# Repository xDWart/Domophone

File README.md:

# Domophone
Релейный модуль расширения на NodeMCU для доработки домофона Wi-Fi'ем и протоколом MQTT

**Eagle** - рабочий проект EagleCAD (v.7.7.0)

**platformio.ini** - ini-файл проекта в среде PlatformIO (редактор Atom)

**src/** - исходные коды прошивки

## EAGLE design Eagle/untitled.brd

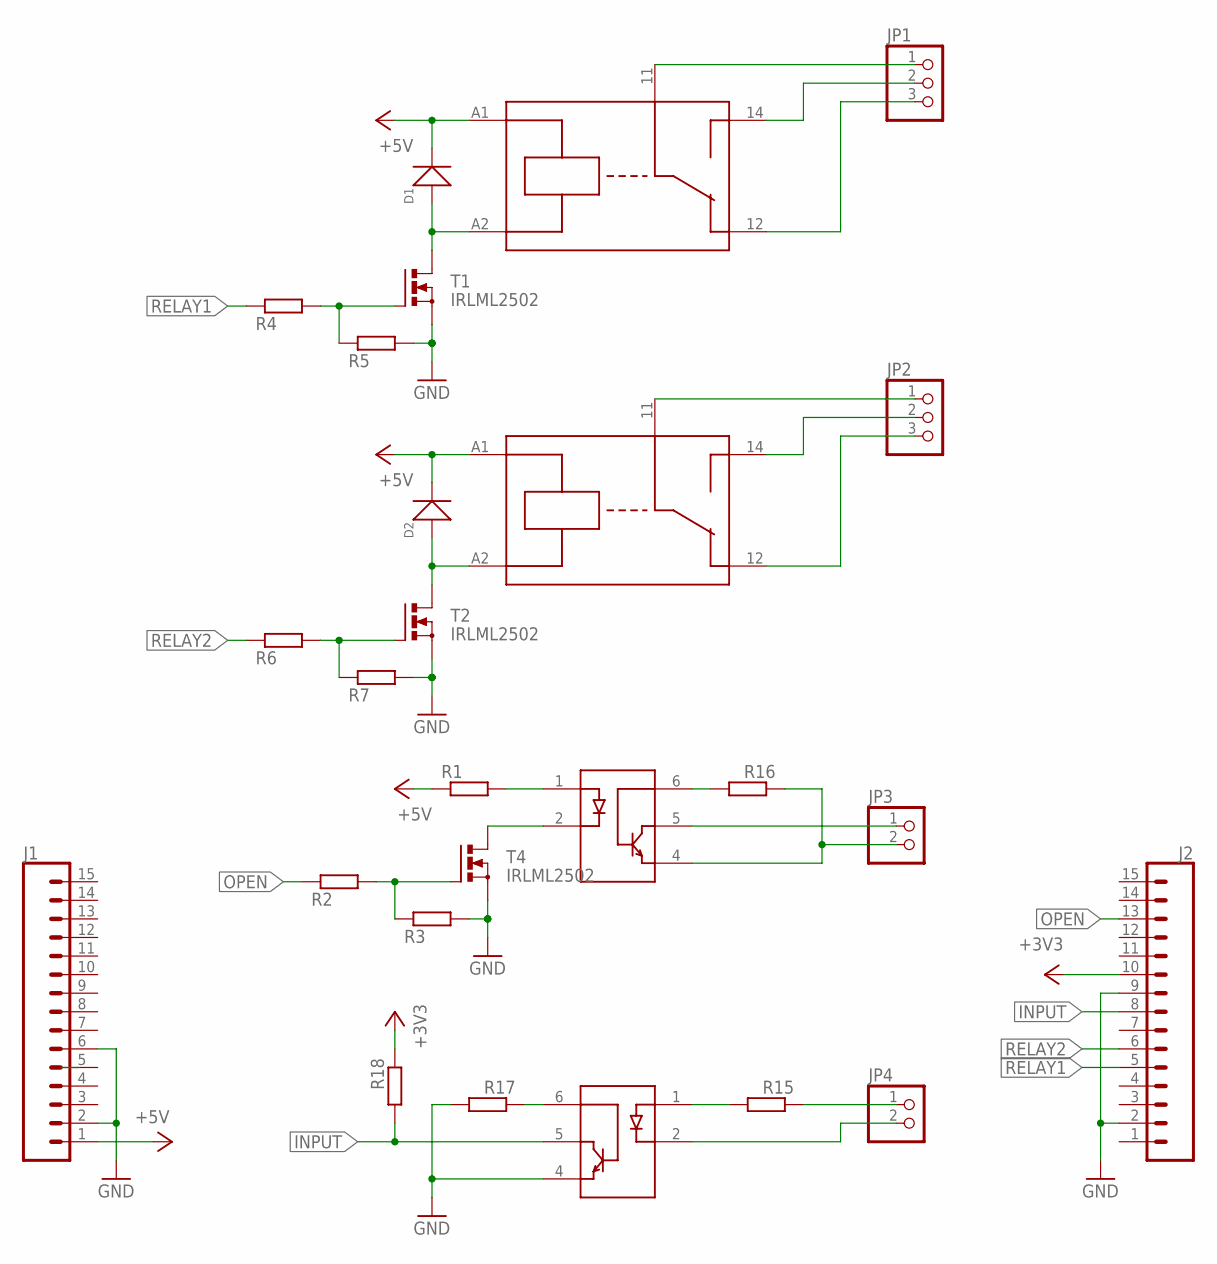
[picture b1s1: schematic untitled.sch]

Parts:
D1, D2: 1N4007; DO-214AC
J1, J2: CONN_15; 1X15
JP1, JP2: PINHD-1X3; 1X03
JP3, JP4: PINHD-1X2; 1X02
R1, R2, R3, R4, R5, R6, R7, R15, R16, R17, R18: R-EU_R0805; R0805
T1, T2, T4: IRLML2502; SOT23
U$5, U$6: PE0140
U$7, U$8: 4N35; DIL06-SMD

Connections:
+3V3: J2.10, R18.1
+5V: D1.2 (-), D2.2 (-), J1.1, R1.1, U$5.A1, U$6.A1
GND: J1.2, J1.6, J2.2, J2.9, R3.2, R5.2, R7.2, R17.2, T1.2 (S), T2.2 (S), T4.2 (S), U$8.4 (E)
INPUT: J2.8, R18.2, U$8.5 (COL)
unnamed: R4.2, R5.1, T1.1 (G)
unnamed: R6.2, R7.1, T2.1 (G)
unnamed: R1.2, U$7.1 (A)
unnamed: T4.3 (D), U$7.2 (CAT)
unnamed: D1.1 (+), T1.3 (D), U$5.A2
unnamed: D2.1 (+), T2.3 (D), U$6.A2
unnamed: R2.2, R3.1, T4.1 (G)
unnamed: JP1.1, U$5.11
unnamed: JP1.2, U$5.14
unnamed: JP1.3, U$5.12
unnamed: JP2.1, U$6.11
unnamed: JP2.2, U$6.14
unnamed: JP2.3, U$6.12
unnamed: JP4.2, U$8.2 (CAT)
unnamed: JP4.1, R15.1
unnamed: R15.2, U$8.1 (A)
unnamed: JP3.1, U$7.5 (COL)
unnamed: JP3.2, R16.1, U$7.4 (E)
unnamed: R16.2, U$7.6 (B)
unnamed: R17.1, U$8.6 (B)
OPEN: J2.13, R2.1
RELAY1: J2.5, R4.1
RELAY2: J2.6, R6.1

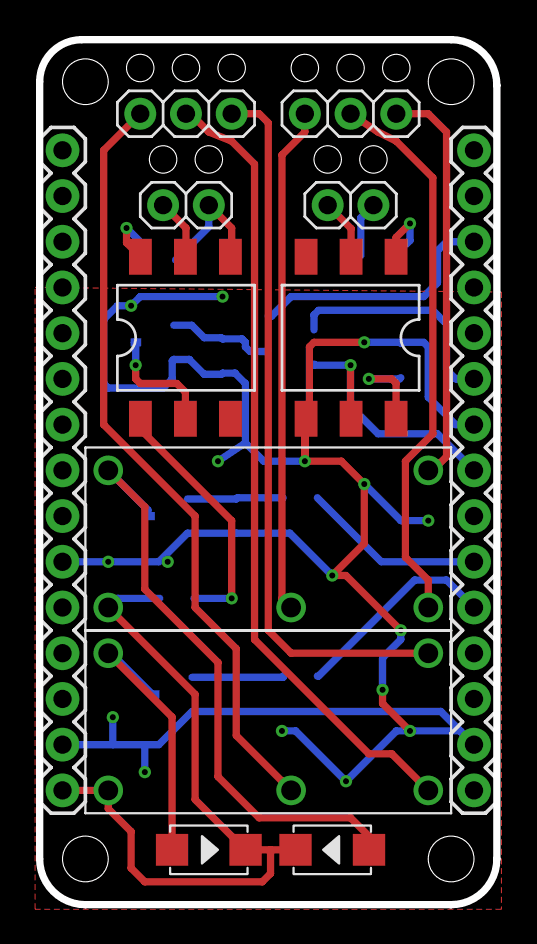
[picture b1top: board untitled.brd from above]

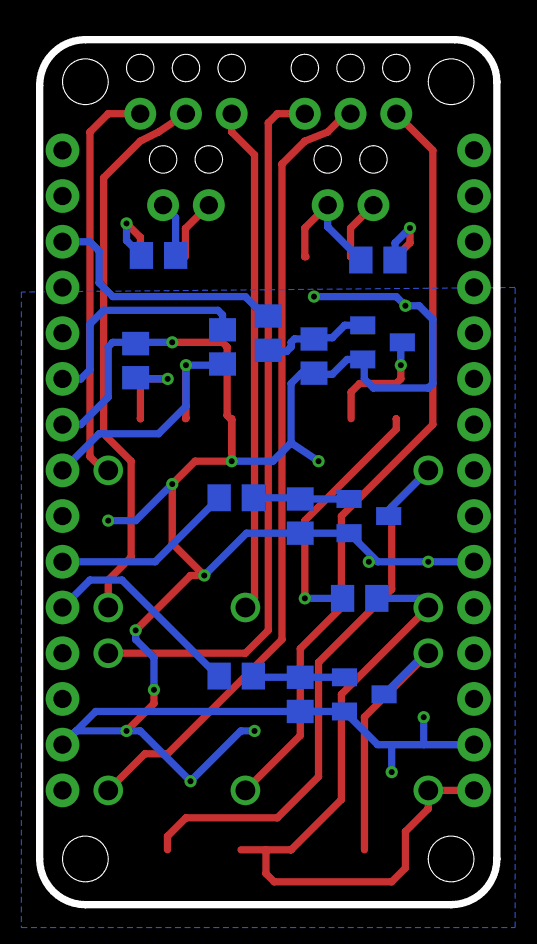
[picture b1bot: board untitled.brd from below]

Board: 2 copper layers, 25.4 x 48.1 mm, 26 parts (14 on the bottom side), 27 nets.

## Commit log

2017-09-04 Init repo for public push
2017-09-07 Rename Relays
2017-10-06 v.2.0
2017-10-08 Switch off sound when openquiet
